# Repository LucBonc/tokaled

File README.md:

**The Tokaled**

During the first pandemic lockdown, starting from The Tokamak Model of Stevie Wray (https://www.thingiverse.com/thing:3264356), is
born the **Tokaled**.
The Tokaled coils (leds) are controlled by an Arduino nano talking via SPI with a raspeberry pi that runs the MARTe2 framework.
The Raspberry feeds the pwm values for TF, CS, PF and Plasma Current leds, using data coming from the **GLORIOUS FTU Tokamak** experimental dataBase (mdsplus trees).

**_Construction Phase:** https://www.thingiverse.com/make:964760:_

<table halign="center">
<tr>
<td>
</center>
</td>
<td>
 
</td>
</tr>
</table>

For the plasma I ve used a transparent pipe rolled up like a helicoid and filled
with an rgb strip.  I connect for IPL the blue light while the PF leds are green, CS are RED, TF are white.

To assemble it, I had to collapse all the TF coils togheter, than I put the plasma pipes inside and I roll it (in an helicoidal way), than I expand again the TF Coils and I put all on the base.

**_Operatin Phase:** https://www.thingiverse.com/make:964745:_

Thera are several Configuration Files with different MARTe2 components to realize differnt Features.

The lights are proportional to the modules of the currents flowing in an FTU experiment.

**A Brief List of HW/SW**

Hardware:
- Rpi2 or better
- picam (not mandatory)
- Arduino Nano
- h-bridge l293d
- 12V or 5V DC RGB led strips (with resistances)
- 5V or 12 V DC power supply

Software:

- https://vcis-gitlab.f4e.europa.eu/aneto/MARTe2 branch develop_armv8_linux
- https://vcis-gitlab.f4e.europa.eu/aneto/MARTe2-components
- https://mdsplus.org
- in this repo you can find arduino firmware, MARTe cfg , jscope file, mdsplus data tree , connection schematic and board, etc...https://github.com/LucBonc/tokaled

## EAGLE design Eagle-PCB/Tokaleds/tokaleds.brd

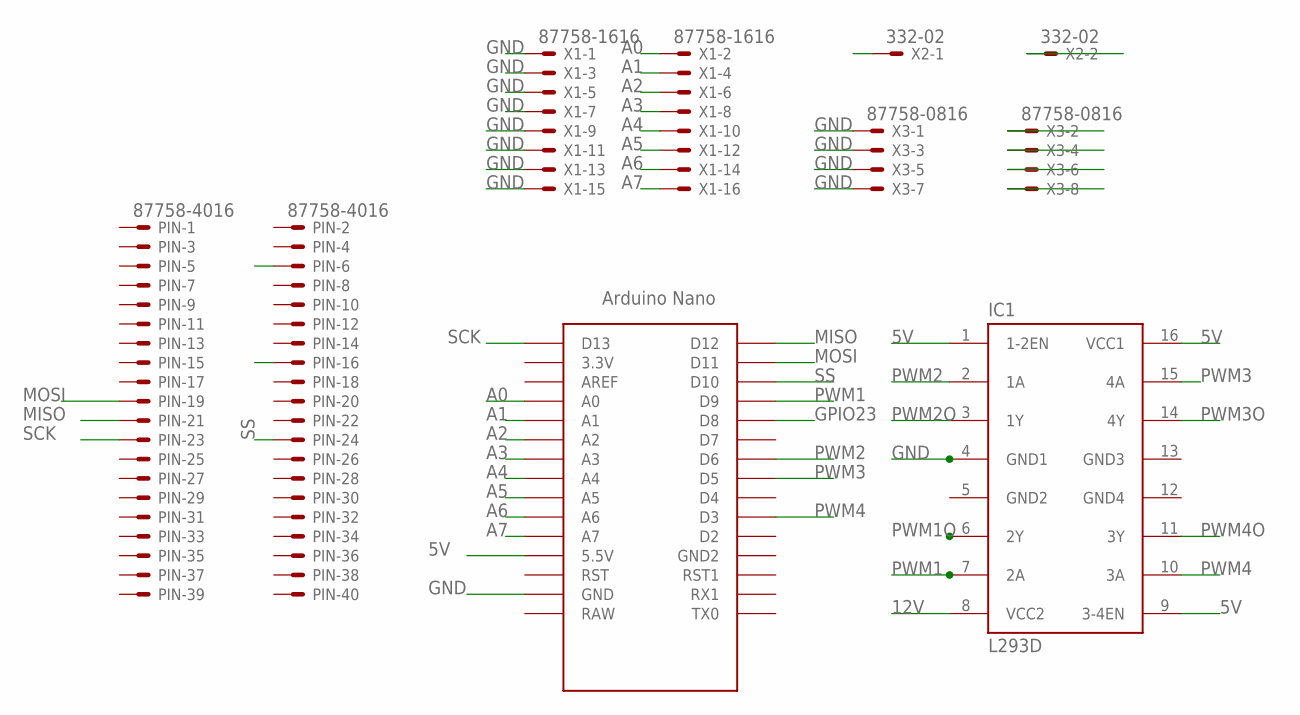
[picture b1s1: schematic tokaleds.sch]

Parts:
IC1: L293D; DIL16
PIN: 87758-4016
U$1: NANO
X1: 87758-1616
X2: 332-02
X3: 87758-0816

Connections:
5V: IC1.1 (1-2EN), IC1.9 (3-4EN), IC1.16 (VCC1), U$1.5V (5.5V)
12V: IC1.8 (VCC2), X2.2
A0: U$1.A0, X1.2
A1: U$1.A1, X1.4
A2: U$1.A2, X1.6
A3: U$1.A3, X1.8
A4: U$1.A4, X1.10
A5: U$1.A5, X1.12
A6: U$1.A6, X1.14
A7: U$1.A7, X1.16
GND: IC1.4 (GND1), PIN.6, U$1.GND, X1.1, X1.3, X1.5, X1.7, X1.9, X1.11, X1.13, X1.15, X2.1, X3.1, X3.3, X3.5, X3.7
GND2: IC1.5 (GND2)
GND3: IC1.13 (GND3)
GND4: IC1.12 (GND4)
GPIO23: PIN.16, U$1.D8
MISO: PIN.21, U$1.D12
MOSI: PIN.19, U$1.D11
PWM1: IC1.7 (2A), U$1.D9
PWM1O: IC1.6 (2Y), X3.2
PWM2: IC1.2 (1A), U$1.D6
PWM2O: IC1.3 (1Y), X3.4
PWM3: IC1.15 (4A), U$1.D5
PWM3O: IC1.14 (4Y), X3.6
PWM4: IC1.10 (3A), U$1.D3
PWM4O: IC1.11 (3Y), X3.8
SCK: PIN.23, U$1.D13
SS: PIN.24, U$1.D10

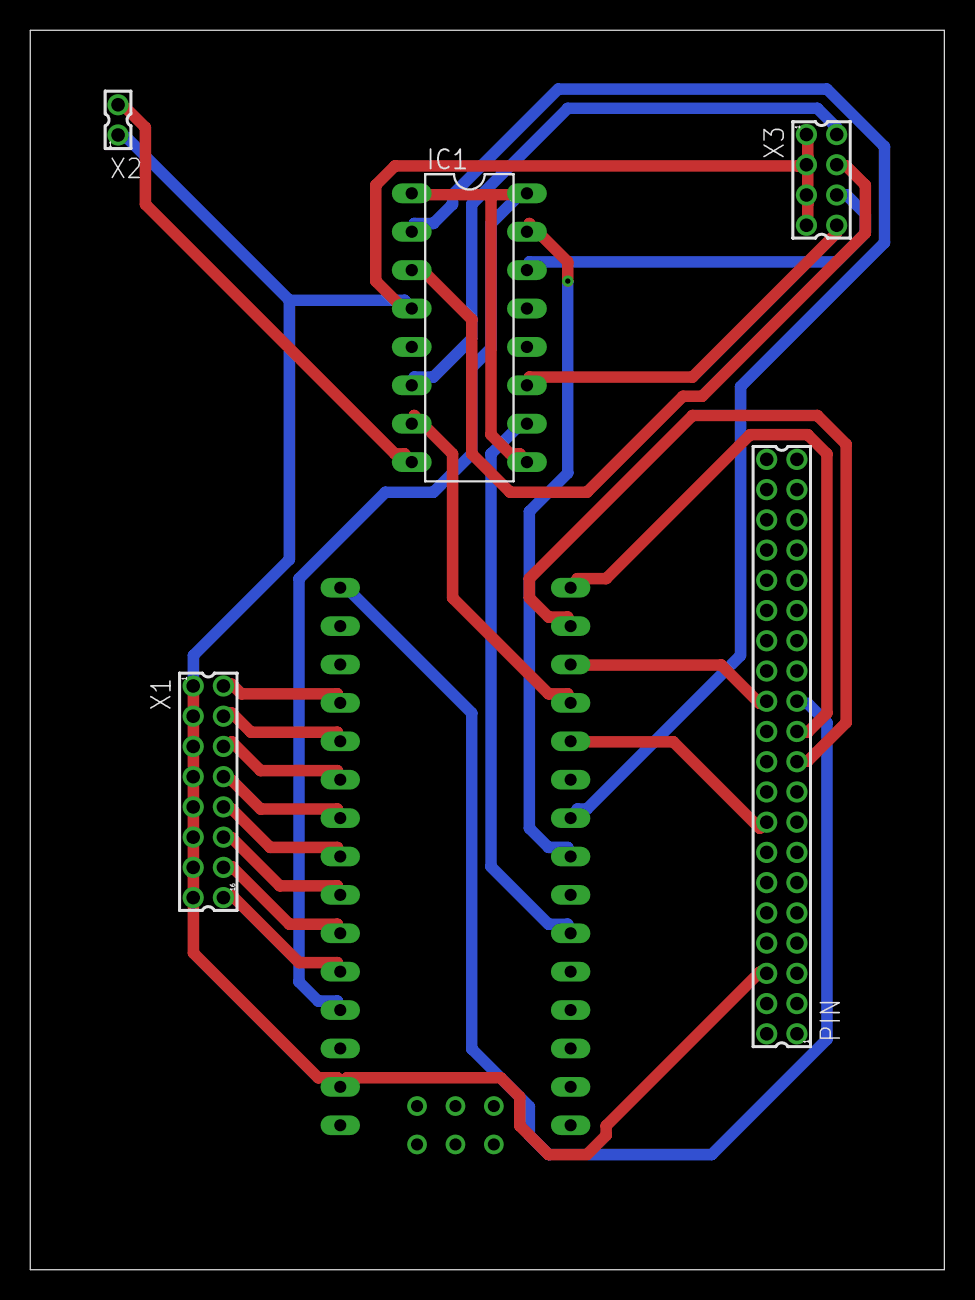
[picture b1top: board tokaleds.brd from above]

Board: 2 copper layers, 60.5 x 82.0 mm, 6 parts (0 on the bottom side), 24 nets.

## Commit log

2021-09-08 Initial Import
2021-09-08 Add minimal README
2021-09-08 Add program to restart marte from GPIO
2021-09-08 remove Build dir
2021-09-08 remove unusefull depfiles
2021-09-08 remove unusefull files ;
2021-09-08 utility restartMARTe2fromGPIO
2021-09-08 Remove unusefull eagle files
2021-09-08 add jScope screenshot
2021-09-15 add pcb schematic jpg
2021-09-15 add pcb schematic png
